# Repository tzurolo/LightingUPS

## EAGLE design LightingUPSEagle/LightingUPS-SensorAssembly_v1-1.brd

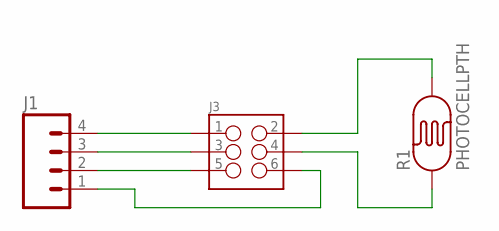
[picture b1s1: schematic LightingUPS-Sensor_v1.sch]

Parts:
J1: M04PTH; 1X04
J3: M03X2SHROUD; 2X3-SHROUDED
R1: PHOTOCELLPTH; PHOTOCELL

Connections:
unnamed: J3.4, R1.1
unnamed: J3.2, R1.2
unnamed: J1.4, J3.1
unnamed: J1.3, J3.3
unnamed: J1.2, J3.5
unnamed: J1.1, J3.6

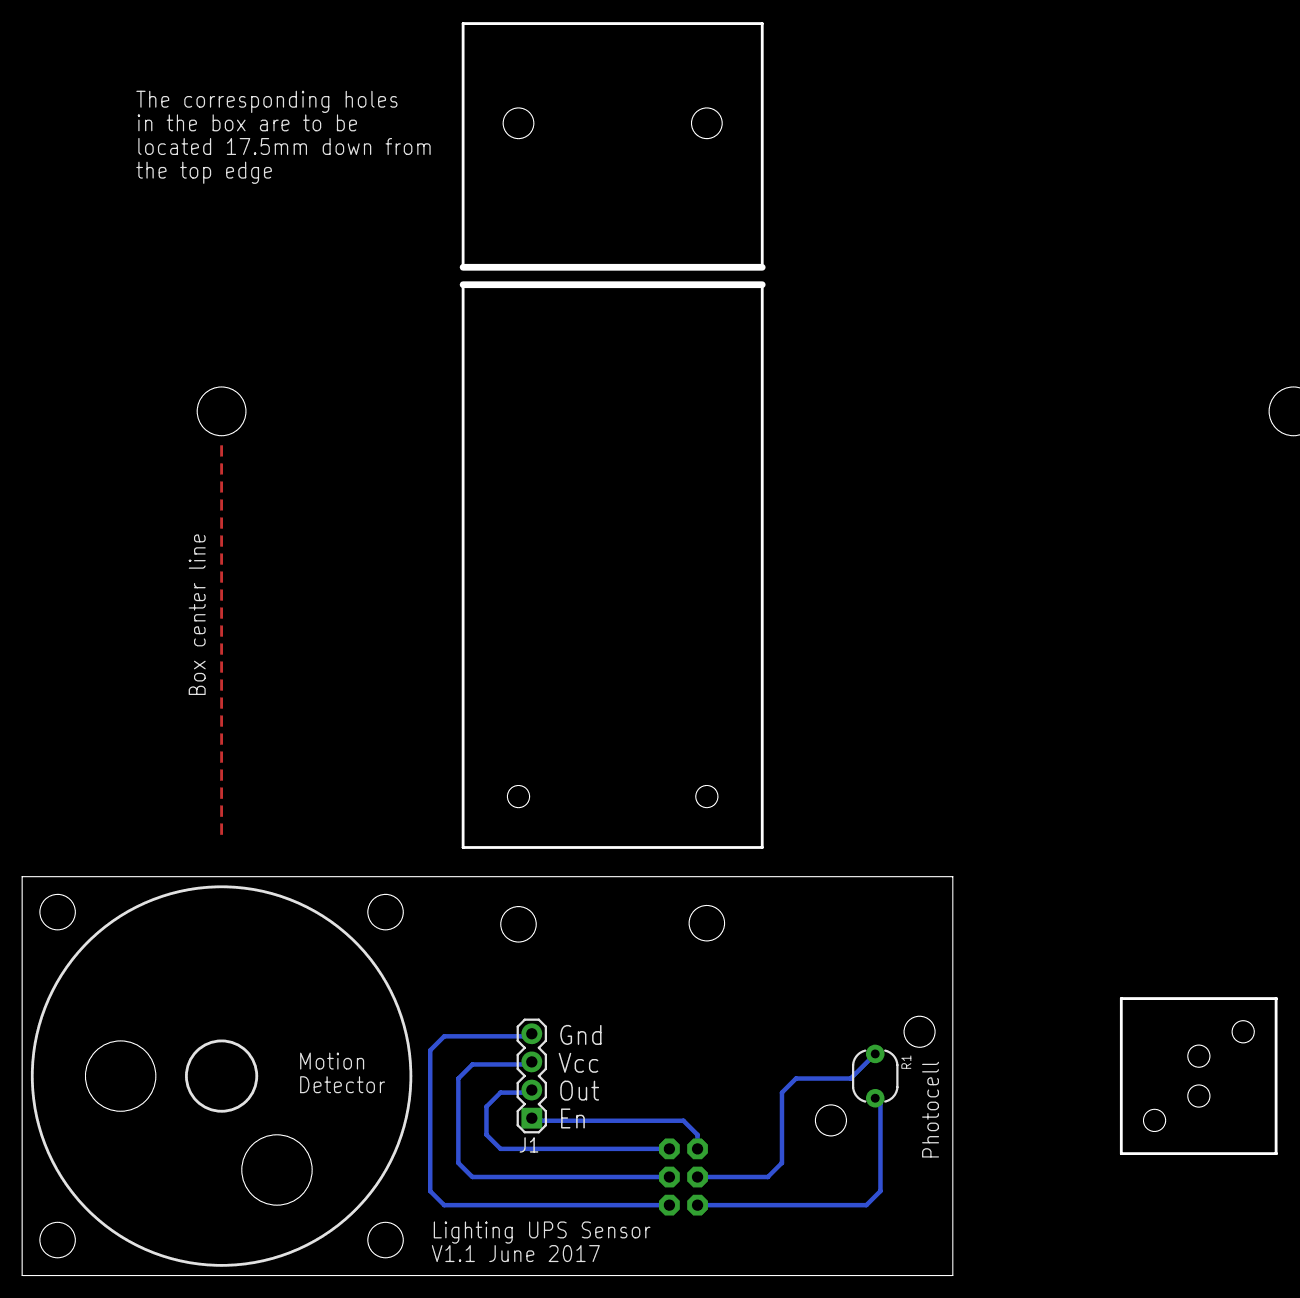
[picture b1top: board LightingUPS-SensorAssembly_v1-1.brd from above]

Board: 2 copper layers, 113.2 x 113.0 mm, 5 parts (1 on the bottom side), 6 nets.

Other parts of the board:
U$1, U$5: DRILL_0.2500

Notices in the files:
parts and their libraries:
SparkFun-Connectors: Licensing: Creative Commons ShareAlike 4.0 International - https://creativecommons.org/licenses/by-sa/4.0
